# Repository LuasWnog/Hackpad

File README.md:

# Hackpad
This my hackpad for listening to music

## Cad Model:
The whole hackpad comes together with 4 M3 heatset inserts and M3 bolts. The PCB fits snugly inside the case, with 2 pegs holding it still. The case comes in two parts, the top and the bottom. The top has holes to allow the rotary encoder, switches, LEDs, and the OLED screen to poke through.

## PCB:
This is the schematic for the PCB (Do note that the pins 1 and 2 and the pins 3 and 4 on the OLED are switched on the schematic),

and this is the PCB itself.

## Firmware and Functions
* The 4 buttons have different functions:
*Previous Track, Pause/Play, Next Track, Mute*
* The rotary encoder will increase and decrease the volume.
* The OLED screen will display the current song, the length of the song, and the next song. (TODO when hardware is received)
* The LEDs will light up according how much of the song that is finished (25%, 50%, 75%, 100%).

The firmware is coded in python with kmk.

## BOM:
Here are all the materials for the hackpad.
* 1x Seeed XIAO RP2040
* 4x MX-Style switches
* 1x EC11 rotary encoder
* 1x 0.91 inch OLED display
* 4x Blank DSA keycaps
* 4x SK6812 MINI-E LEDs
* 4x M3x16mm screws
* 4x - M3x5mx4mm heatset inserts
* 1x 3D printed case

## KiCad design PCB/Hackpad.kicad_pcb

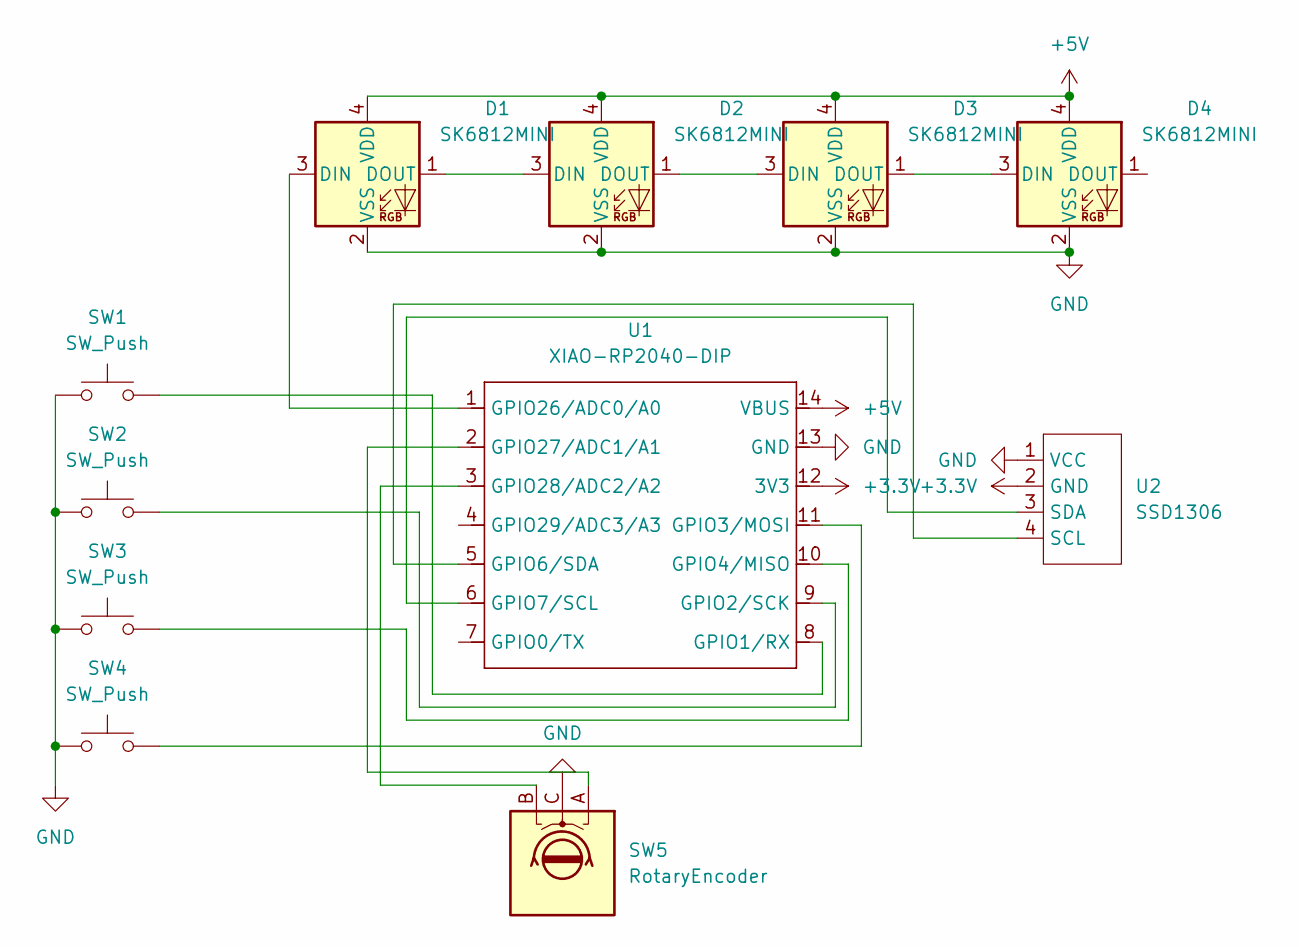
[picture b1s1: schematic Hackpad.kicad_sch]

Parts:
D1, D2, D3, D4: SK6812MINI; LED_SK6812MINI_PLCC4_3.5x3.5mm_P1.75mm
SW1, SW2, SW3, SW4: SW_Push; SW_Cherry_MX_1.00u_PCB
SW5: RotaryEncoder; RotaryEncoder_Alps_EC11E_Vertical_H20mm
U1: XIAO-RP2040-DIP
U2: SSD1306; SSD1306-0.91-OLED-4pin-128x32

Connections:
+3.3V: U1.12 (3V3), U2.2 (GND)
+5V: D1.4 (VDD), D2.4 (VDD), D3.4 (VDD), D4.4 (VDD), U1.14 (VBUS)
GND: D1.2 (VSS), D2.2 (VSS), D3.2 (VSS), D4.2 (VSS), SW1.1, SW2.1, SW3.1, SW4.1, SW5.C, U1.13 (GND), U2.1 (VCC)
unnamed: D1.3 (DIN), U1.1 (GPIO26/ADC0/A0)
unnamed: D1.1 (DOUT), D2.3 (DIN)
unnamed: D2.1 (DOUT), D3.3 (DIN)
unnamed: D3.1 (DOUT), D4.3 (DIN)
unnamed: SW1.2, U1.8 (GPIO1/RX)
unnamed: SW2.2, U1.9 (GPIO2/SCK)
unnamed: SW4.2, U1.11 (GPIO3/MOSI)
unnamed: SW3.2, U1.10 (GPIO4/MISO)
unnamed: U1.5 (GPIO6/SDA), U2.4 (SCL)
unnamed: U1.6 (GPIO7/SCL), U2.3 (SDA)
unnamed: SW5.A, U1.2 (GPIO27/ADC1/A1)
unnamed: SW5.B, U1.3 (GPIO28/ADC2/A2)

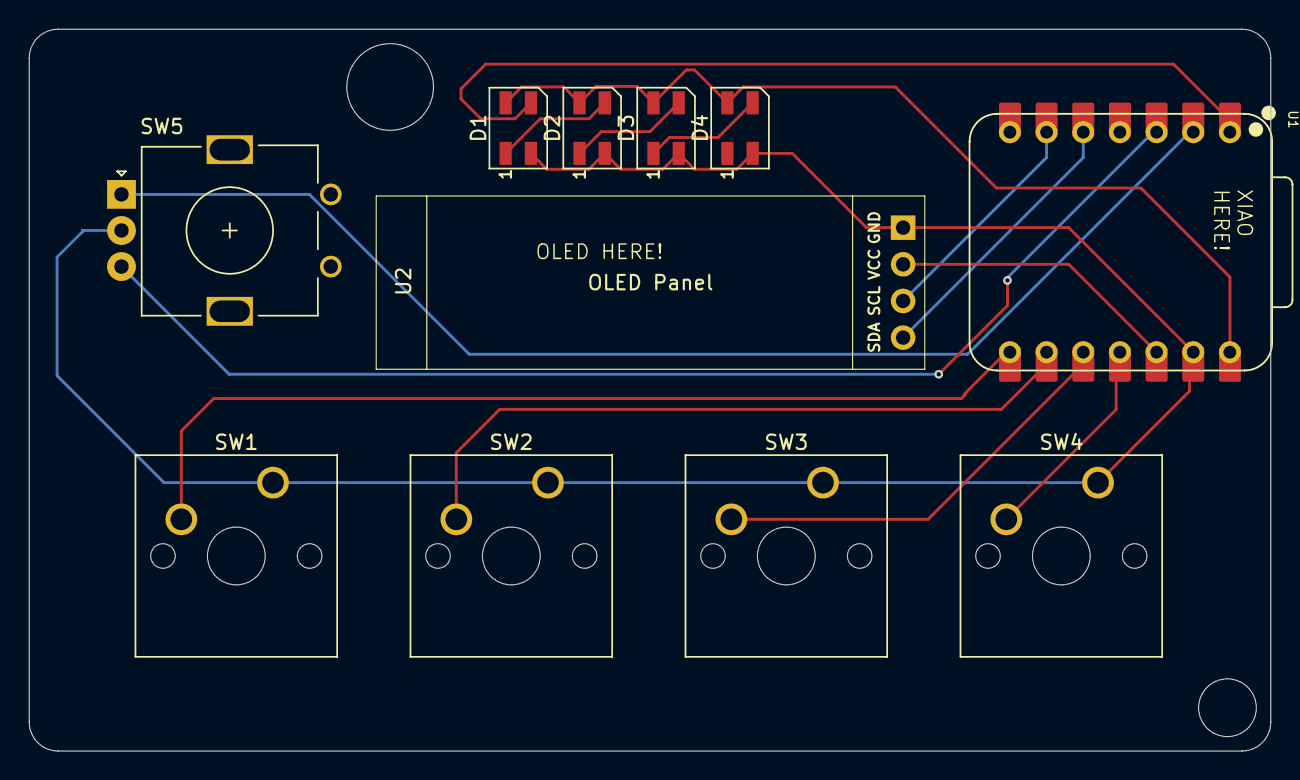
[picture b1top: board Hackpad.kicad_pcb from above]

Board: 2 copper layers, 86.0 x 50.0 mm, 11 parts (0 on the bottom side), 15 nets.

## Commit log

2025-12-13 Created the KiCad files
2025-12-13 Created schematic and PCB
    PCB is still not routed.
2025-12-14 Routed PCB
    Routed PCB and finished overall PCB construction
2025-12-15 Created the case for the PCB
    Contains top and bottom of case. STL files.
2025-12-15 Created assembled and firmware
    Created assembled step file, removed case bottom and hackpad stl
2025-12-16 Programmed Firmware
    Configured firmware, 4 switches and rotary encoder assigned, programmed OLED
2025-12-16 Categorised files into respective folders
    Three folders, CAD, Firmware, and PCB
2025-12-18 Created README and updated some parts
    Updated PCBs and step model
2025-12-18 Removed obsidian files
2026-01-10 Redoing photos in README
2026-01-17 Connected the OLED to 3.3V instead of 5V
2026-01-17 Rearranged pins on the OLED
2026-02-06 Gerber files made
